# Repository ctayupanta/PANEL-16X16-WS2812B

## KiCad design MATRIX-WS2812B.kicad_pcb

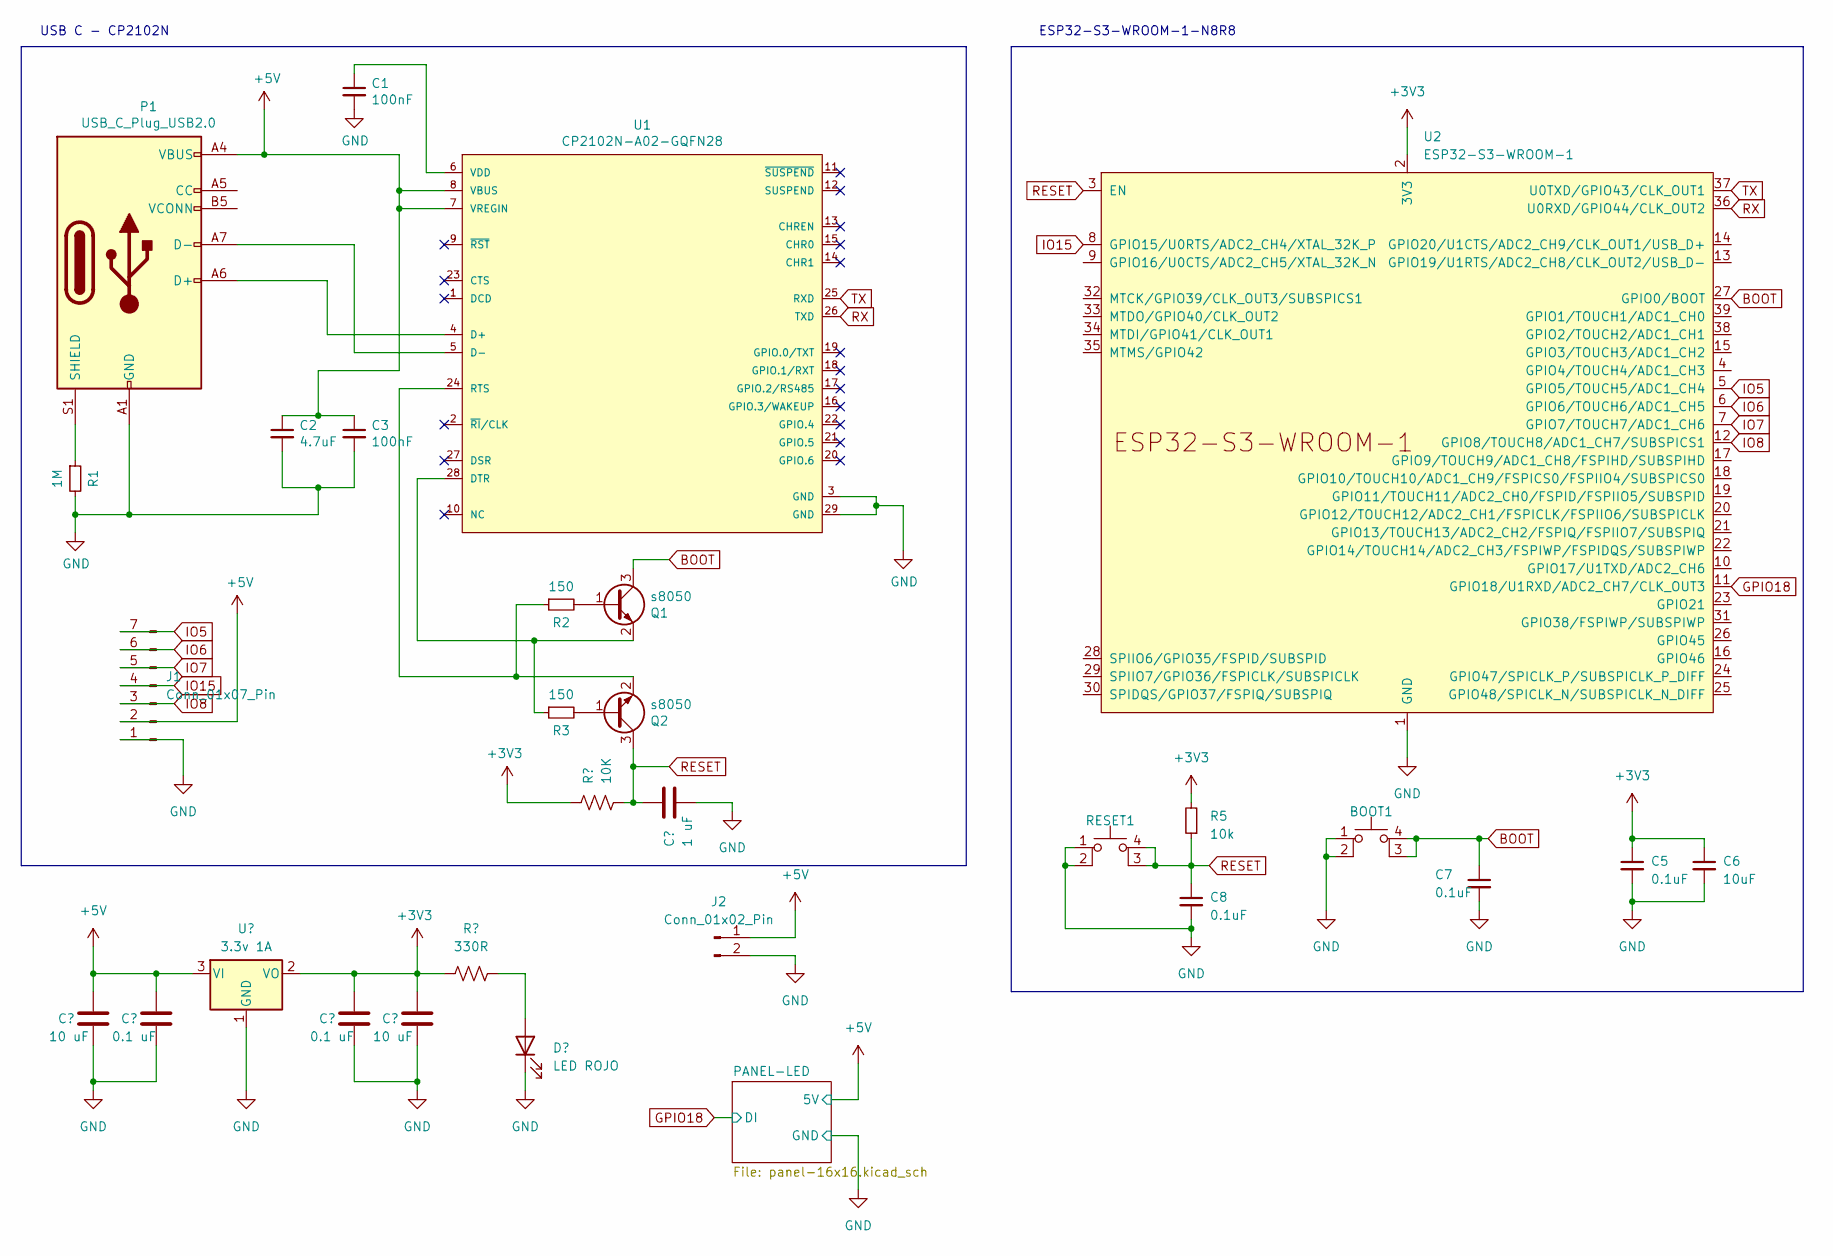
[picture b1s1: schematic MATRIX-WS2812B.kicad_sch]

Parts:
BOOT1: SW_Tactile_SPST_NO_Straight_CK_PTS636Sx25SMTRLFS
C1, C3: 100nF; C_0805_2012Metric
C2: 4.7uF; C_0805_2012Metric
C4: 1 uF; C_0805_2012Metric
C5, C7, C8: 0.1uF; C_0805_2012Metric
C6: 10uF; C_0805_2012Metric
C9, C12: 10 uF; C_0805_2012Metric
C10, C11: 0.1 uF; C_0805_2012Metric
D1: LED ROJO; LED_0805_2012Metric
J1: Conn_01x07_Pin; PinHeader_1x07_P2.54mm_Vertical
J2: Conn_01x02_Pin; PinHeader_1x02_P2.54mm_Vertical
P1: USB_C_Plug_USB2.0; USB_C_Receptacle_GCT_USB4110
Q1, Q2: s8050; SOT-23
R1: 1M; R_0805_2012Metric
R2, R3: 150; R_0805_2012Metric
R4: 10K; R_0805_2012Metric
R5: 10k; R_0805_2012Metric
R6: 330R; R_0805_2012Metric
RESET1: SW_Tactile_SPST_NO_Straight_CK_PTS636Sx25SMTRLFS
U1: CP2102N-A02-GQFN28; QFN50P500X500X80-29N; mouser part number 634-CP2102NA02GQFN28; digikey description IC USB TO UART BRIDGE QFN28
U2: ESP32-S3-WROOM-1
U3: 3.3v 1A; SOT-223-3_TabPin2

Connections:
+3V3: C5.1, C6.1, C11.1, C12.1, R4.2, R5.2, R6.1, U2.2 (3V3), U3.2 (VO)
+5V: C2.1, C3.1, C9.1, C10.1, J1.2, J2.1, P1.A4 (VBUS), P1.A9 (VBUS), P1.B4 (VBUS), P1.B9 (VBUS), U1.7 (VREGIN), U1.8 (VBUS), U3.3 (VI); also elsewhere on the board
BOOT: BOOT1.3 (K), BOOT1.4 (A), C7.1, Q1.3 (C), U2.27 (GPIO0/BOOT)
GND: BOOT1.1, BOOT1.2, C1.2, C2.2, C3.2, C4.2, C5.2, C6.2, C7.2, C8.2, C9.2, C10.2, C11.2, C12.2, D1.1 (K), J1.1, J2.2, P1.A1 (GND), P1.A12 (GND), P1.B1 (GND), P1.B12 (GND), R1.2, RESET1.1, RESET1.2, U1.3 (GND), U1.29 (GND), U2.1 (GND), U2.40 (GND), U2.41 (GND), U3.1 (GND); also elsewhere on the board
GPIO18: U2.11 (GPIO18/U1RXD/ADC2_CH7/CLK_OUT3); also elsewhere on the board
IO5: J1.7, U2.5 (GPIO5/TOUCH5/ADC1_CH4)
IO6: J1.6, U2.6 (GPIO6/TOUCH6/ADC1_CH5)
IO7: J1.5, U2.7 (GPIO7/TOUCH7/ADC1_CH6)
IO8: J1.3, U2.12 (GPIO8/TOUCH8/ADC1_CH7/SUBSPICS1)
IO15: J1.4, U2.8 (GPIO15/U0RTS/ADC2_CH4/XTAL_32K_P)
unnamed: D1.2 (A), R6.2
unnamed: P1.A6 (D+), U1.4 (D+)
unnamed: P1.A7 (D-), U1.5 (D-)
unnamed: P1.S1 (SHIELD), R1.1
unnamed: Q1.1 (B), R2.2
unnamed: Q1.2 (E), R3.1, U1.28 (DTR)
unnamed: Q2.1 (B), R3.2
unnamed: Q2.2 (E), R2.1, U1.24 (RTS)
unnamed: C1.1, U1.6 (VDD)
RESET: C4.1, C8.1, Q2.3 (C), R4.1, R5.1, RESET1.3 (K), RESET1.4 (A), U2.3 (EN)
RX: U1.26 (TXD), U2.36 (U0RXD/GPIO44/CLK_OUT2)
TX: U1.25 (RXD), U2.37 (U0TXD/GPIO43/CLK_OUT1)

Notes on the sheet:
USB C - CP2102N
ESP32-S3-WROOM-1-N8R8

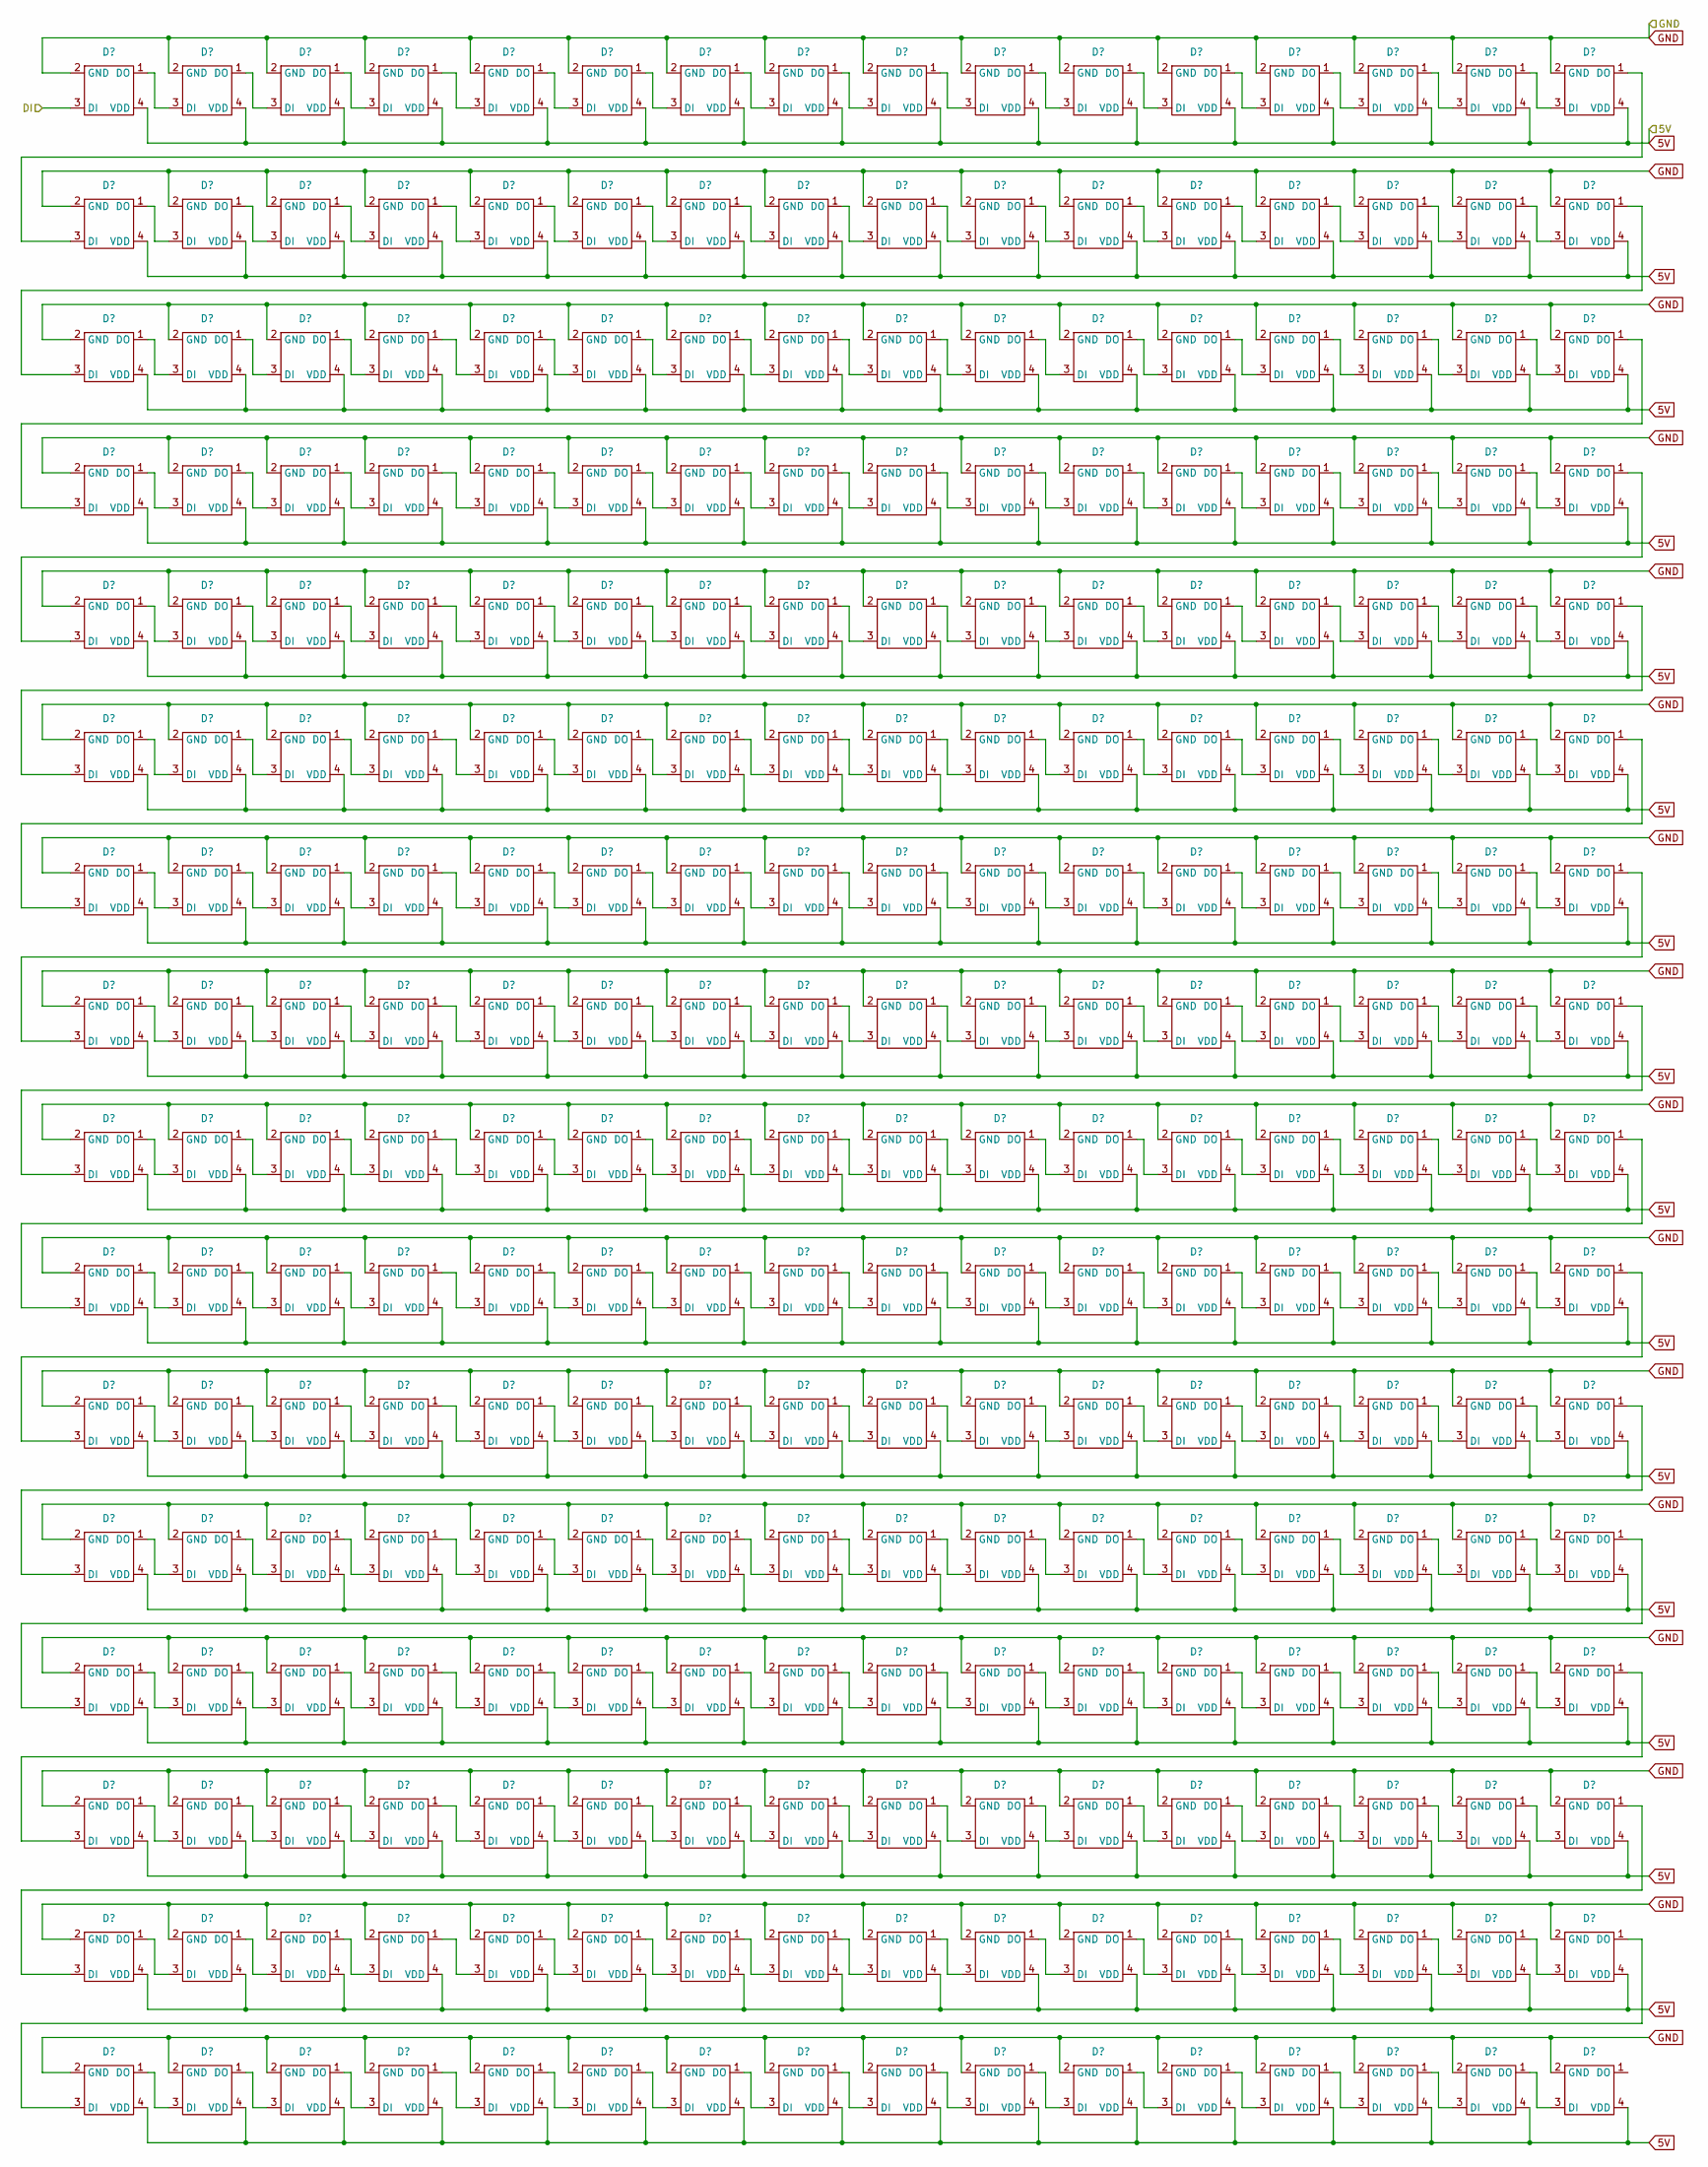
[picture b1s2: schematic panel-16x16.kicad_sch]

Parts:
D2, D3, D4, D5, D6, D7, D8, D9, D10, D11, D12, D13, D14, D15, D16, D17, D18, D19, D20, D21, D22, D23, D24, D25, D26, D27, D28, D29, D30, D31, D32, D33, D34, D35, D36, D37, D38, D39, D40, D41, D42, D43, D44, D45, D46, D47, D48, D49, D50, D51, D52, D53, D54, D55, D56, D57, D58, D59, D60, D61, D62, D63, D64, D65, D66, D67, D68, D69, D70, D71, D72, D73, D74, D75, D76, D77, D78, D79, D80, D81, D82, D83, D84, D85, D86, D87, D88, D89, D90, D91, D92, D93, D94, D95, D96, D97, D98, D99, D100, D101, D102, D103, D104, D105, D106, D107, D108, D109, D110, D111, D112, D113, D114, D115, D116, D117, D118, D119, D120, D121, D122, D123, D124, D125, D126, D127, D128, D129, D130, D131, D132, D133, D134, D135, D136, D137, D138, D139, D140, D141, D142, D143, D144, D145, D146, D147, D148, D149, D150, D151, D152, D153, D154, D155, D156, D157, D158, D159, D160, D161, D162, D163, D164, D165, D166, D167, D168, D169, D170, D171, D172, D173, D174, D175, D176, D177, D178, D179, D180, D181, D182, D183, D184, D185, D186, D187, D188, D189, D190, D191, D192, D193, D194, D195, D196, D197, D198, D199, D200, D201, D202, D203, D204, D205, D206, D207, D208, D209, D210, D211, D212, D213, D214, D215, D216, D217, D218, D219, D220, D221, D222, D223, D224, D225, D226, D227, D228, D229, D230, D231, D232, D233, D234, D235, D236, D237, D238, D239, D240, D241, D242, D243, D244, D245, D246, D247, D248, D249, D250, D251, D252, D253, D254, D255, D256, D257: LED-WS2812B-2020

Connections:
+5V: D2.4 (VDD), D3.4 (VDD), D4.4 (VDD), D5.4 (VDD), D6.4 (VDD), D7.4 (VDD), D8.4 (VDD), D9.4 (VDD), D10.4 (VDD), D11.4 (VDD), D12.4 (VDD), D13.4 (VDD), D14.4 (VDD), D15.4 (VDD), D16.4 (VDD), D17.4 (VDD), D18.4 (VDD), D19.4 (VDD), D20.4 (VDD), D21.4 (VDD), D22.4 (VDD), D23.4 (VDD), D24.4 (VDD), D25.4 (VDD), D26.4 (VDD), D27.4 (VDD), D28.4 (VDD), D29.4 (VDD), D30.4 (VDD), D31.4 (VDD), D32.4 (VDD), D33.4 (VDD), D34.4 (VDD), D35.4 (VDD), D36.4 (VDD), D37.4 (VDD), D38.4 (VDD), D39.4 (VDD), D40.4 (VDD), D41.4 (VDD), D42.4 (VDD), D43.4 (VDD), D44.4 (VDD), D45.4 (VDD), D46.4 (VDD), D47.4 (VDD), D48.4 (VDD), D49.4 (VDD), D50.4 (VDD), D51.4 (VDD), D52.4 (VDD), D53.4 (VDD), D54.4 (VDD), D55.4 (VDD), D56.4 (VDD), D57.4 (VDD), D58.4 (VDD), D59.4 (VDD), D60.4 (VDD), D61.4 (VDD), D62.4 (VDD), D63.4 (VDD), D64.4 (VDD), D65.4 (VDD), D66.4 (VDD), D67.4 (VDD), D68.4 (VDD), D69.4 (VDD), D70.4 (VDD), D71.4 (VDD), D72.4 (VDD), D73.4 (VDD), D74.4 (VDD), D75.4 (VDD), D76.4 (VDD), D77.4 (VDD), D78.4 (VDD), D79.4 (VDD), D80.4 (VDD), D81.4 (VDD), D82.4 (VDD), D83.4 (VDD), D84.4 (VDD), D85.4 (VDD), D86.4 (VDD), D87.4 (VDD), D88.4 (VDD), D89.4 (VDD), D90.4 (VDD), D91.4 (VDD), D92.4 (VDD), D93.4 (VDD), D94.4 (VDD), D95.4 (VDD), D96.4 (VDD), D97.4 (VDD), D98.4 (VDD), D99.4 (VDD), D100.4 (VDD), D101.4 (VDD), D102.4 (VDD), D103.4 (VDD), D104.4 (VDD), D105.4 (VDD), D106.4 (VDD), D107.4 (VDD), D108.4 (VDD), D109.4 (VDD), D110.4 (VDD), D111.4 (VDD), D112.4 (VDD), D113.4 (VDD), D114.4 (VDD), D115.4 (VDD), D116.4 (VDD), D117.4 (VDD), D118.4 (VDD), D119.4 (VDD), D120.4 (VDD), D121.4 (VDD), D122.4 (VDD), D123.4 (VDD), D124.4 (VDD), D125.4 (VDD), D126.4 (VDD), D127.4 (VDD), D128.4 (VDD), D129.4 (VDD), D130.4 (VDD), D131.4 (VDD), D132.4 (VDD), D133.4 (VDD), D134.4 (VDD), D135.4 (VDD), D136.4 (VDD), D137.4 (VDD), D138.4 (VDD), D139.4 (VDD), D140.4 (VDD), D141.4 (VDD), D142.4 (VDD), D143.4 (VDD), D144.4 (VDD), D145.4 (VDD), D146.4 (VDD), D147.4 (VDD), D148.4 (VDD), D149.4 (VDD), D150.4 (VDD), D151.4 (VDD), D152.4 (VDD), D153.4 (VDD), D154.4 (VDD), D155.4 (VDD), D156.4 (VDD), D157.4 (VDD), D158.4 (VDD), D159.4 (VDD), D160.4 (VDD), D161.4 (VDD), D162.4 (VDD), D163.4 (VDD), D164.4 (VDD), D165.4 (VDD), D166.4 (VDD), D167.4 (VDD), D168.4 (VDD), D169.4 (VDD), D170.4 (VDD), D171.4 (VDD), D172.4 (VDD), D173.4 (VDD), D174.4 (VDD), D175.4 (VDD), D176.4 (VDD), D177.4 (VDD), D178.4 (VDD), D179.4 (VDD), D180.4 (VDD), D181.4 (VDD), D182.4 (VDD), D183.4 (VDD), D184.4 (VDD), D185.4 (VDD), D186.4 (VDD), D187.4 (VDD), D188.4 (VDD), D189.4 (VDD), D190.4 (VDD), D191.4 (VDD), D192.4 (VDD), D193.4 (VDD), D194.4 (VDD), D195.4 (VDD), D196.4 (VDD), D197.4 (VDD), D198.4 (VDD), D199.4 (VDD), D200.4 (VDD), D201.4 (VDD), D202.4 (VDD), D203.4 (VDD), D204.4 (VDD), D205.4 (VDD), D206.4 (VDD), D207.4 (VDD), D208.4 (VDD), D209.4 (VDD), D210.4 (VDD), D211.4 (VDD), D212.4 (VDD), D213.4 (VDD), D214.4 (VDD), D215.4 (VDD), D216.4 (VDD), D217.4 (VDD), D218.4 (VDD), D219.4 (VDD), D220.4 (VDD), D221.4 (VDD), D222.4 (VDD), D223.4 (VDD), D224.4 (VDD), D225.4 (VDD), D226.4 (VDD), D227.4 (VDD), D228.4 (VDD), D229.4 (VDD), D230.4 (VDD), D231.4 (VDD), D232.4 (VDD), D233.4 (VDD), D234.4 (VDD), D235.4 (VDD), D236.4 (VDD), D237.4 (VDD), D238.4 (VDD), D239.4 (VDD), D240.4 (VDD), D241.4 (VDD), D242.4 (VDD), D243.4 (VDD), D244.4 (VDD), D245.4 (VDD), D246.4 (VDD), D247.4 (VDD), D248.4 (VDD), D249.4 (VDD), D250.4 (VDD), D251.4 (VDD), D252.4 (VDD), D253.4 (VDD), D254.4 (VDD), D255.4 (VDD), D256.4 (VDD), D257.4 (VDD); also elsewhere on the board
GND: D2.2 (GND), D3.2 (GND), D4.2 (GND), D5.2 (GND), D6.2 (GND), D7.2 (GND), D8.2 (GND), D9.2 (GND), D10.2 (GND), D11.2 (GND), D12.2 (GND), D13.2 (GND), D14.2 (GND), D15.2 (GND), D16.2 (GND), D17.2 (GND), D18.2 (GND), D19.2 (GND), D20.2 (GND), D21.2 (GND), D22.2 (GND), D23.2 (GND), D24.2 (GND), D25.2 (GND), D26.2 (GND), D27.2 (GND), D28.2 (GND), D29.2 (GND), D30.2 (GND), D31.2 (GND), D32.2 (GND), D33.2 (GND), D34.2 (GND), D35.2 (GND), D36.2 (GND), D37.2 (GND), D38.2 (GND), D39.2 (GND), D40.2 (GND), D41.2 (GND), D42.2 (GND), D43.2 (GND), D44.2 (GND), D45.2 (GND), D46.2 (GND), D47.2 (GND), D48.2 (GND), D49.2 (GND), D50.2 (GND), D51.2 (GND), D52.2 (GND), D53.2 (GND), D54.2 (GND), D55.2 (GND), D56.2 (GND), D57.2 (GND), D58.2 (GND), D59.2 (GND), D60.2 (GND), D61.2 (GND), D62.2 (GND), D63.2 (GND), D64.2 (GND), D65.2 (GND), D66.2 (GND), D67.2 (GND), D68.2 (GND), D69.2 (GND), D70.2 (GND), D71.2 (GND), D72.2 (GND), D73.2 (GND), D74.2 (GND), D75.2 (GND), D76.2 (GND), D77.2 (GND), D78.2 (GND), D79.2 (GND), D80.2 (GND), D81.2 (GND), D82.2 (GND), D83.2 (GND), D84.2 (GND), D85.2 (GND), D86.2 (GND), D87.2 (GND), D88.2 (GND), D89.2 (GND), D90.2 (GND), D91.2 (GND), D92.2 (GND), D93.2 (GND), D94.2 (GND), D95.2 (GND), D96.2 (GND), D97.2 (GND), D98.2 (GND), D99.2 (GND), D100.2 (GND), D101.2 (GND), D102.2 (GND), D103.2 (GND), D104.2 (GND), D105.2 (GND), D106.2 (GND), D107.2 (GND), D108.2 (GND), D109.2 (GND), D110.2 (GND), D111.2 (GND), D112.2 (GND), D113.2 (GND), D114.2 (GND), D115.2 (GND), D116.2 (GND), D117.2 (GND), D118.2 (GND), D119.2 (GND), D120.2 (GND), D121.2 (GND), D122.2 (GND), D123.2 (GND), D124.2 (GND), D125.2 (GND), D126.2 (GND), D127.2 (GND), D128.2 (GND), D129.2 (GND), D130.2 (GND), D131.2 (GND), D132.2 (GND), D133.2 (GND), D134.2 (GND), D135.2 (GND), D136.2 (GND), D137.2 (GND), D138.2 (GND), D139.2 (GND), D140.2 (GND), D141.2 (GND), D142.2 (GND), D143.2 (GND), D144.2 (GND), D145.2 (GND), D146.2 (GND), D147.2 (GND), D148.2 (GND), D149.2 (GND), D150.2 (GND), D151.2 (GND), D152.2 (GND), D153.2 (GND), D154.2 (GND), D155.2 (GND), D156.2 (GND), D157.2 (GND), D158.2 (GND), D159.2 (GND), D160.2 (GND), D161.2 (GND), D162.2 (GND), D163.2 (GND), D164.2 (GND), D165.2 (GND), D166.2 (GND), D167.2 (GND), D168.2 (GND), D169.2 (GND), D170.2 (GND), D171.2 (GND), D172.2 (GND), D173.2 (GND), D174.2 (GND), D175.2 (GND), D176.2 (GND), D177.2 (GND), D178.2 (GND), D179.2 (GND), D180.2 (GND), D181.2 (GND), D182.2 (GND), D183.2 (GND), D184.2 (GND), D185.2 (GND), D186.2 (GND), D187.2 (GND), D188.2 (GND), D189.2 (GND), D190.2 (GND), D191.2 (GND), D192.2 (GND), D193.2 (GND), D194.2 (GND), D195.2 (GND), D196.2 (GND), D197.2 (GND), D198.2 (GND), D199.2 (GND), D200.2 (GND), D201.2 (GND), D202.2 (GND), D203.2 (GND), D204.2 (GND), D205.2 (GND), D206.2 (GND), D207.2 (GND), D208.2 (GND), D209.2 (GND), D210.2 (GND), D211.2 (GND), D212.2 (GND), D213.2 (GND), D214.2 (GND), D215.2 (GND), D216.2 (GND), D217.2 (GND), D218.2 (GND), D219.2 (GND), D220.2 (GND), D221.2 (GND), D222.2 (GND), D223.2 (GND), D224.2 (GND), D225.2 (GND), D226.2 (GND), D227.2 (GND), D228.2 (GND), D229.2 (GND), D230.2 (GND), D231.2 (GND), D232.2 (GND), D233.2 (GND), D234.2 (GND), D235.2 (GND), D236.2 (GND), D237.2 (GND), D238.2 (GND), D239.2 (GND), D240.2 (GND), D241.2 (GND), D242.2 (GND), D243.2 (GND), D244.2 (GND), D245.2 (GND), D246.2 (GND), D247.2 (GND), D248.2 (GND), D249.2 (GND), D250.2 (GND), D251.2 (GND), D252.2 (GND), D253.2 (GND), D254.2 (GND), D255.2 (GND), D256.2 (GND), D257.2 (GND); also elsewhere on the board
GPIO18: D2.3 (DI); also elsewhere on the board
unnamed: D2.1 (DO), D3.3 (DI)
unnamed: D3.1 (DO), D4.3 (DI)
unnamed: D4.1 (DO), D5.3 (DI)
unnamed: D5.1 (DO), D6.3 (DI)
unnamed: D6.1 (DO), D7.3 (DI)
unnamed: D7.1 (DO), D8.3 (DI)
unnamed: D8.1 (DO), D9.3 (DI)
unnamed: D9.1 (DO), D10.3 (DI)
unnamed: D10.1 (DO), D11.3 (DI)
unnamed: D11.1 (DO), D12.3 (DI)
unnamed: D12.1 (DO), D13.3 (DI)
unnamed: D13.1 (DO), D14.3 (DI)
unnamed: D14.1 (DO), D15.3 (DI)
unnamed: D15.1 (DO), D16.3 (DI)
unnamed: D16.1 (DO), D17.3 (DI)
unnamed: D17.1 (DO), D18.3 (DI)
unnamed: D18.1 (DO), D19.3 (DI)
unnamed: D19.1 (DO), D20.3 (DI)
unnamed: D20.1 (DO), D21.3 (DI)
unnamed: D21.1 (DO), D22.3 (DI)
unnamed: D22.1 (DO), D23.3 (DI)
unnamed: D23.1 (DO), D24.3 (DI)
unnamed: D24.1 (DO), D25.3 (DI)
unnamed: D25.1 (DO), D26.3 (DI)
unnamed: D26.1 (DO), D27.3 (DI)
unnamed: D27.1 (DO), D28.3 (DI)
unnamed: D28.1 (DO), D29.3 (DI)
unnamed: D29.1 (DO), D30.3 (DI)
unnamed: D30.1 (DO), D31.3 (DI)
unnamed: D31.1 (DO), D32.3 (DI)
unnamed: D32.1 (DO), D33.3 (DI)
unnamed: D33.1 (DO), D34.3 (DI)
unnamed: D34.1 (DO), D35.3 (DI)
unnamed: D35.1 (DO), D36.3 (DI)
unnamed: D36.1 (DO), D37.3 (DI)
unnamed: D37.1 (DO), D38.3 (DI)
unnamed: D38.1 (DO), D39.3 (DI)
unnamed: D39.1 (DO), D40.3 (DI)
unnamed: D40.1 (DO), D41.3 (DI)
unnamed: D41.1 (DO), D42.3 (DI)
unnamed: D42.1 (DO), D43.3 (DI)
unnamed: D43.1 (DO), D44.3 (DI)
unnamed: D44.1 (DO), D45.3 (DI)
unnamed: D45.1 (DO), D46.3 (DI)
unnamed: D46.1 (DO), D47.3 (DI)
unnamed: D47.1 (DO), D48.3 (DI)
unnamed: D48.1 (DO), D49.3 (DI)
unnamed: D49.1 (DO), D50.3 (DI)
unnamed: D50.1 (DO), D51.3 (DI)
unnamed: D51.1 (DO), D52.3 (DI)
unnamed: D52.1 (DO), D53.3 (DI)
unnamed: D53.1 (DO), D54.3 (DI)
unnamed: D54.1 (DO), D55.3 (DI)
unnamed: D55.1 (DO), D56.3 (DI)
unnamed: D56.1 (DO), D57.3 (DI)
unnamed: D57.1 (DO), D58.3 (DI)
unnamed: D58.1 (DO), D59.3 (DI)
unnamed: D59.1 (DO), D60.3 (DI)
unnamed: D60.1 (DO), D61.3 (DI)
unnamed: D61.1 (DO), D62.3 (DI)
unnamed: D62.1 (DO), D63.3 (DI)
unnamed: D63.1 (DO), D64.3 (DI)
unnamed: D64.1 (DO), D65.3 (DI)
unnamed: D65.1 (DO), D66.3 (DI)
unnamed: D66.1 (DO), D67.3 (DI)
unnamed: D67.1 (DO), D68.3 (DI)
unnamed: D68.1 (DO), D69.3 (DI)
unnamed: D69.1 (DO), D70.3 (DI)
unnamed: D70.1 (DO), D71.3 (DI)
unnamed: D71.1 (DO), D72.3 (DI)
unnamed: D72.1 (DO), D73.3 (DI)
unnamed: D73.1 (DO), D74.3 (DI)
unnamed: D74.1 (DO), D75.3 (DI)
unnamed: D75.1 (DO), D76.3 (DI)
unnamed: D76.1 (DO), D77.3 (DI)
unnamed: D77.1 (DO), D78.3 (DI)
unnamed: D78.1 (DO), D79.3 (DI)
unnamed: D79.1 (DO), D80.3 (DI)
unnamed: D80.1 (DO), D81.3 (DI)
unnamed: D81.1 (DO), D82.3 (DI)
unnamed: D82.1 (DO), D83.3 (DI)
unnamed: D83.1 (DO), D84.3 (DI)
unnamed: D84.1 (DO), D85.3 (DI)
unnamed: D85.1 (DO), D86.3 (DI)
unnamed: D86.1 (DO), D87.3 (DI)
unnamed: D87.1 (DO), D88.3 (DI)
unnamed: D88.1 (DO), D89.3 (DI)
unnamed: D89.1 (DO), D90.3 (DI)
unnamed: D90.1 (DO), D91.3 (DI)
unnamed: D91.1 (DO), D92.3 (DI)
unnamed: D92.1 (DO), D93.3 (DI)
unnamed: D93.1 (DO), D94.3 (DI)
unnamed: D94.1 (DO), D95.3 (DI)
unnamed: D95.1 (DO), D96.3 (DI)
unnamed: D96.1 (DO), D97.3 (DI)
unnamed: D97.1 (DO), D98.3 (DI)
unnamed: D98.1 (DO), D99.3 (DI)
unnamed: D99.1 (DO), D100.3 (DI)
unnamed: D100.1 (DO), D101.3 (DI)
unnamed: D101.1 (DO), D102.3 (DI)
unnamed: D102.1 (DO), D103.3 (DI)
unnamed: D103.1 (DO), D104.3 (DI)
unnamed: D104.1 (DO), D105.3 (DI)
unnamed: D105.1 (DO), D106.3 (DI)
unnamed: D106.1 (DO), D107.3 (DI)
unnamed: D107.1 (DO), D108.3 (DI)
unnamed: D108.1 (DO), D109.3 (DI)
unnamed: D109.1 (DO), D110.3 (DI)
unnamed: D110.1 (DO), D111.3 (DI)
unnamed: D111.1 (DO), D112.3 (DI)
unnamed: D112.1 (DO), D113.3 (DI)
unnamed: D113.1 (DO), D114.3 (DI)
unnamed: D114.1 (DO), D115.3 (DI)
unnamed: D115.1 (DO), D116.3 (DI)
unnamed: D116.1 (DO), D117.3 (DI)
unnamed: D117.1 (DO), D118.3 (DI)
unnamed: D118.1 (DO), D119.3 (DI)
unnamed: D119.1 (DO), D120.3 (DI)
unnamed: D120.1 (DO), D121.3 (DI)
unnamed: D121.1 (DO), D122.3 (DI)
unnamed: D122.1 (DO), D123.3 (DI)
unnamed: D123.1 (DO), D124.3 (DI)
unnamed: D124.1 (DO), D125.3 (DI)
unnamed: D125.1 (DO), D126.3 (DI)
unnamed: D126.1 (DO), D127.3 (DI)
unnamed: D127.1 (DO), D128.3 (DI)
unnamed: D128.1 (DO), D129.3 (DI)
unnamed: D129.1 (DO), D130.3 (DI)
unnamed: D130.1 (DO), D131.3 (DI)
unnamed: D131.1 (DO), D132.3 (DI)
unnamed: D132.1 (DO), D133.3 (DI)
unnamed: D133.1 (DO), D134.3 (DI)
unnamed: D134.1 (DO), D135.3 (DI)
unnamed: D135.1 (DO), D136.3 (DI)
unnamed: D136.1 (DO), D137.3 (DI)
unnamed: D137.1 (DO), D138.3 (DI)
unnamed: D138.1 (DO), D139.3 (DI)
unnamed: D139.1 (DO), D140.3 (DI)
unnamed: D140.1 (DO), D141.3 (DI)
unnamed: D141.1 (DO), D142.3 (DI)
unnamed: D142.1 (DO), D143.3 (DI)
unnamed: D143.1 (DO), D144.3 (DI)
unnamed: D144.1 (DO), D145.3 (DI)
unnamed: D145.1 (DO), D146.3 (DI)
unnamed: D146.1 (DO), D147.3 (DI)
unnamed: D147.1 (DO), D148.3 (DI)
unnamed: D148.1 (DO), D149.3 (DI)
unnamed: D149.1 (DO), D150.3 (DI)
unnamed: D150.1 (DO), D151.3 (DI)
unnamed: D151.1 (DO), D152.3 (DI)
unnamed: D152.1 (DO), D153.3 (DI)
unnamed: D153.1 (DO), D154.3 (DI)
unnamed: D154.1 (DO), D155.3 (DI)
unnamed: D155.1 (DO), D156.3 (DI)
unnamed: D156.1 (DO), D157.3 (DI)
unnamed: D157.1 (DO), D158.3 (DI)
unnamed: D158.1 (DO), D159.3 (DI)
unnamed: D159.1 (DO), D160.3 (DI)
unnamed: D160.1 (DO), D161.3 (DI)
unnamed: D161.1 (DO), D162.3 (DI)
unnamed: D162.1 (DO), D163.3 (DI)
unnamed: D163.1 (DO), D164.3 (DI)
unnamed: D164.1 (DO), D165.3 (DI)
unnamed: D165.1 (DO), D166.3 (DI)
unnamed: D166.1 (DO), D167.3 (DI)
unnamed: D167.1 (DO), D168.3 (DI)
unnamed: D168.1 (DO), D169.3 (DI)
unnamed: D169.1 (DO), D170.3 (DI)
unnamed: D170.1 (DO), D171.3 (DI)
unnamed: D171.1 (DO), D172.3 (DI)
unnamed: D172.1 (DO), D173.3 (DI)
unnamed: D173.1 (DO), D174.3 (DI)
unnamed: D174.1 (DO), D175.3 (DI)
unnamed: D175.1 (DO), D176.3 (DI)
unnamed: D176.1 (DO), D177.3 (DI)
unnamed: D177.1 (DO), D178.3 (DI)
unnamed: D178.1 (DO), D179.3 (DI)
unnamed: D179.1 (DO), D180.3 (DI)
unnamed: D180.1 (DO), D181.3 (DI)
unnamed: D181.1 (DO), D182.3 (DI)
unnamed: D182.1 (DO), D183.3 (DI)
unnamed: D183.1 (DO), D184.3 (DI)
unnamed: D184.1 (DO), D185.3 (DI)
unnamed: D185.1 (DO), D186.3 (DI)
unnamed: D186.1 (DO), D187.3 (DI)
unnamed: D187.1 (DO), D188.3 (DI)
unnamed: D188.1 (DO), D189.3 (DI)
unnamed: D189.1 (DO), D190.3 (DI)
unnamed: D190.1 (DO), D191.3 (DI)
unnamed: D191.1 (DO), D192.3 (DI)
unnamed: D192.1 (DO), D193.3 (DI)
unnamed: D193.1 (DO), D194.3 (DI)
unnamed: D194.1 (DO), D195.3 (DI)
unnamed: D195.1 (DO), D196.3 (DI)
unnamed: D196.1 (DO), D197.3 (DI)
unnamed: D197.1 (DO), D198.3 (DI)
unnamed: D198.1 (DO), D199.3 (DI)
unnamed: D199.1 (DO), D200.3 (DI)
unnamed: D200.1 (DO), D201.3 (DI)
unnamed: D201.1 (DO), D202.3 (DI)
unnamed: D202.1 (DO), D203.3 (DI)
unnamed: D203.1 (DO), D204.3 (DI)
unnamed: D204.1 (DO), D205.3 (DI)
unnamed: D205.1 (DO), D206.3 (DI)
unnamed: D206.1 (DO), D207.3 (DI)
unnamed: D207.1 (DO), D208.3 (DI)
unnamed: D208.1 (DO), D209.3 (DI)
unnamed: D209.1 (DO), D210.3 (DI)
unnamed: D210.1 (DO), D211.3 (DI)
unnamed: D211.1 (DO), D212.3 (DI)
unnamed: D212.1 (DO), D213.3 (DI)
unnamed: D213.1 (DO), D214.3 (DI)
unnamed: D214.1 (DO), D215.3 (DI)
unnamed: D215.1 (DO), D216.3 (DI)
unnamed: D216.1 (DO), D217.3 (DI)
unnamed: D217.1 (DO), D218.3 (DI)
unnamed: D218.1 (DO), D219.3 (DI)
unnamed: D219.1 (DO), D220.3 (DI)
unnamed: D220.1 (DO), D221.3 (DI)
unnamed: D221.1 (DO), D222.3 (DI)
unnamed: D222.1 (DO), D223.3 (DI)
unnamed: D223.1 (DO), D224.3 (DI)
unnamed: D224.1 (DO), D225.3 (DI)
unnamed: D225.1 (DO), D226.3 (DI)
unnamed: D226.1 (DO), D227.3 (DI)
unnamed: D227.1 (DO), D228.3 (DI)
unnamed: D228.1 (DO), D229.3 (DI)
unnamed: D229.1 (DO), D230.3 (DI)
unnamed: D230.1 (DO), D231.3 (DI)
unnamed: D231.1 (DO), D232.3 (DI)
unnamed: D232.1 (DO), D233.3 (DI)
unnamed: D233.1 (DO), D234.3 (DI)
unnamed: D234.1 (DO), D235.3 (DI)
unnamed: D235.1 (DO), D236.3 (DI)
unnamed: D236.1 (DO), D237.3 (DI)
unnamed: D237.1 (DO), D238.3 (DI)
unnamed: D238.1 (DO), D239.3 (DI)
unnamed: D239.1 (DO), D240.3 (DI)
unnamed: D240.1 (DO), D241.3 (DI)
unnamed: D241.1 (DO), D242.3 (DI)
unnamed: D242.1 (DO), D243.3 (DI)
unnamed: D243.1 (DO), D244.3 (DI)
unnamed: D244.1 (DO), D245.3 (DI)
unnamed: D245.1 (DO), D246.3 (DI)
unnamed: D246.1 (DO), D247.3 (DI)
unnamed: D247.1 (DO), D248.3 (DI)
unnamed: D248.1 (DO), D249.3 (DI)
unnamed: D249.1 (DO), D250.3 (DI)
unnamed: D250.1 (DO), D251.3 (DI)
unnamed: D251.1 (DO), D252.3 (DI)
unnamed: D252.1 (DO), D253.3 (DI)
unnamed: D253.1 (DO), D254.3 (DI)
unnamed: D254.1 (DO), D255.3 (DI)
unnamed: D255.1 (DO), D256.3 (DI)
unnamed: D256.1 (DO), D257.3 (DI)

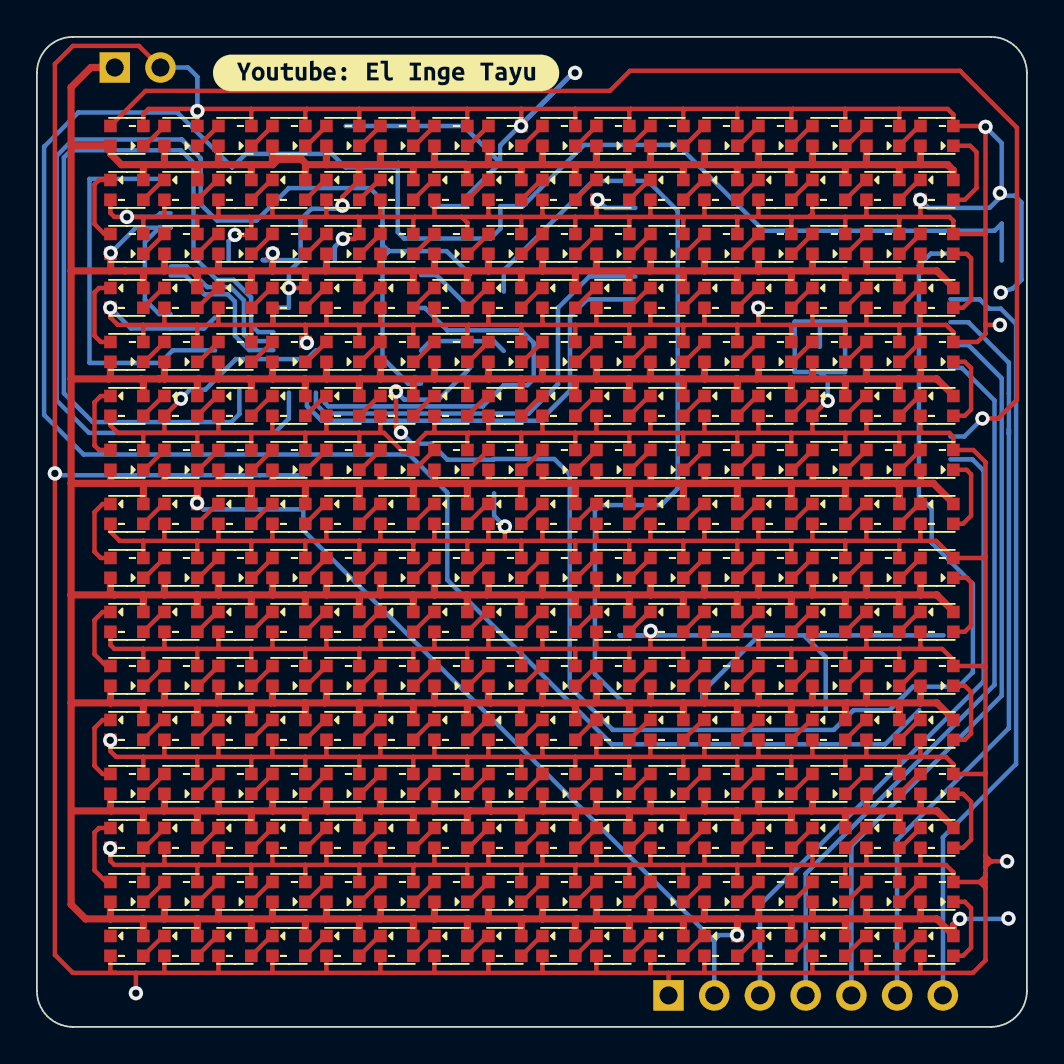
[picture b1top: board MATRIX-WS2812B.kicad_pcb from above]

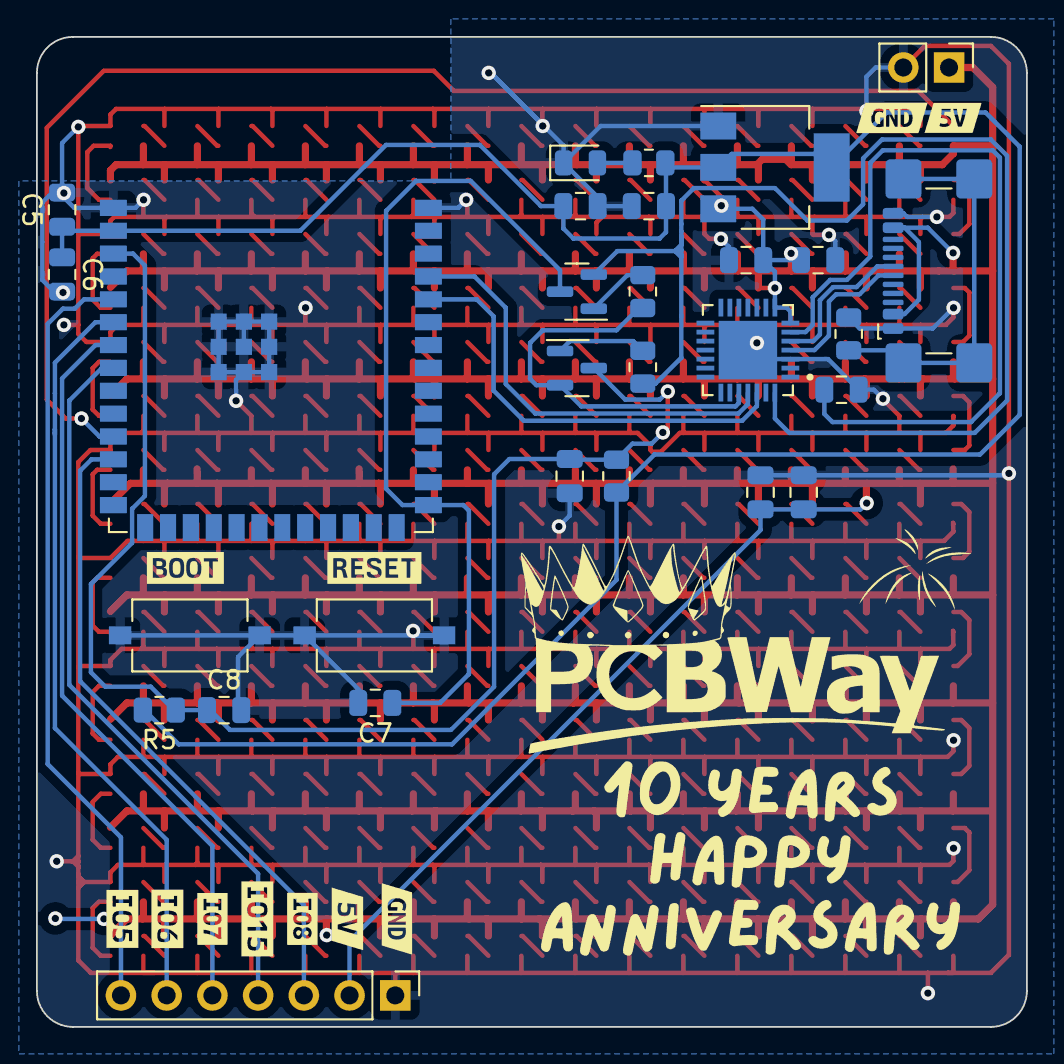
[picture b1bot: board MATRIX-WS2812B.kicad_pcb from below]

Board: 2 copper layers, 55.0 x 55.0 mm, 297 parts (40 on the bottom side), 277 nets.

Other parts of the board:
kibuzzard-6615B07E: G***; kibuzzard-6615B07E
kibuzzard-6615B101: G***; kibuzzard-6615B101
kibuzzard-66130A0A: G***; kibuzzard-66130A0A
kibuzzard-66130C0E: G***; kibuzzard-66130C0E
kibuzzard-66130C55: G***; kibuzzard-66130C55
kibuzzard-66130C91: G***; kibuzzard-66130C91
kibuzzard-66130D16: G***; kibuzzard-66130D16
kibuzzard-661309B7: G***; kibuzzard-661309B7
kibuzzard-661325A7: G***; kibuzzard-661325A7
kibuzzard-661369FD: G***; kibuzzard-661369FD
kibuzzard-66157906: G***; kibuzzard-66157906
kibuzzard-66157932: G***; kibuzzard-66157932

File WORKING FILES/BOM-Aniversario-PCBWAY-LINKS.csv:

"Reference","Value","Footprint","Link Vendor","Cdad"
"BOOT1","~","Button_Switch_SMD:SW_Tactile_SPST_NO_Straight_CK_PTS636Sx25SMTRLFS","","1"
"C1, C3","100nF","Capacitor_SMD:C_0805_2012Metric","https://www.lcsc.com/product-detail/Multilayer-Ceramic-Capac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","2"
"C2","4.7uF","Capacitor_SMD:C_0805_2012Metric","https://www.lcsc.com/product-detail/Multilayer-Ceramic-Capac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","1"
"C4","1 uF","Capacitor_SMD:C_0805_2012Metric","https://www.lcsc.com/product-detail/Multilayer-Ceramic-Capac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","1"
"C5, C7, C8","0.1uF","Capacitor_SMD:C_0805_2012Metric","https://www.lcsc.com/product-detail/Multilayer-Ceramic-Capac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","3"
"C6","10uF","Capacitor_SMD:C_0805_2012Metric","https://www.lcsc.com/product-detail/Multilayer-Ceramic-Capac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","1"
"C9, C12","10 uF","Capacitor_SMD:C_0805_2012Metric","https://www.lcsc.com/product-detail/Multilayer-Ceramic-Capac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","2"
"C10, C11","0.1 uF","Capacitor_SMD:C_0805_2012Metric","https://www.lcsc.com/product-detail/Multilayer-Ceramic-Capac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","2"
"D1","LED ROJO","LED_SMD:LED_0805_2012Metric","https://www.lcsc.com/product-detail/Light-Emitting-Diodes-sp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","1"
"D2-D257","~","led-WS2812B-2020:LED-WS2812B-2020","https://www.lcsc.com/product-detail/Light-Emitting-Diodes-LE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","256"
"J1","Conn_01x07_Pin","Connector_PinHeader_2.54mm:PinHeader_1x07_P2.54mm_Vertical","","1"
"J2","Conn_01x02_Pin","Connector_PinHeader_2.54mm:PinHeader_1x02_P2.54mm_Vertical","","1"
"P1","USB_C_Plug_USB2.0","Connector_USB:USB_C_Receptacle_GCT_USB4110","https://www.lcsc.com/product-detail/span-style-background-co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","1"
"Q1, Q2","s8050","Package_TO_SOT_SMD:SOT-23","https://www.lcsc.com/product-detail/Bipolar-Transistors-BJT_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","2"
"R1","1M","Resistor_SMD:R_0805_2012Metric","https://www.lcsc.com/product-detail/Chip-span-style-backgrou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","1"
"R2, R3","150","Resistor_SMD:R_0805_2012Metric","https://www.lcsc.com/product-detail/Chip-span-style-backgrou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","2"
"R4","10K","Resistor_SMD:R_0805_2012Metric","https://www.lcsc.com/product-detail/Chip-span-style-backgrou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","1"
"R5","10k","Resistor_SMD:R_0805_2012Metric","https://www.lcsc.com/product-detail/Chip-span-style-backgrou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","1"
"R6","330R","Resistor_SMD:R_0805_2012Metric","https://www.lcsc.com/product-detail/Chip-span-style-backgrou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","1"
"RESET1","~","Button_Switch_SMD:SW_Tactile_SPST_NO_Straight_CK_PTS636Sx25SMTRLFS","https://www.lcsc.com/product-detail/Tactile-Switches_C-K-PTS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","1"
"U1","CP2102N-A02-GQFN28","CP2102N-A02:QFN50P500X500X80-29N","https://www.lcsc.com/product-detail/USB-ICs_SKYWORKS-SILICON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","1"
"U2","ESP32-S3-WROOM-1","PCM_Espressif:ESP32-S3-WROOM-1","https://www.lcsc.com/product-detail/WiFi-Modules_Espressif-S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","1"
"U3","3.3v 1A","Package_TO_SOT_SMD:SOT-223-3_TabPin2","https://www.lcsc.com/product-detail/Linear-Voltage-Regulator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","1"
